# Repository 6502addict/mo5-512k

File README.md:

# mo5-512k
MO5 512K Cartridge
<br>

<br>
## Description
this cartridge is compatible with thomson MO5 64k cartridge
it's not a exact copy of the original cartridge<br>
but rather a rebuild from the manual
<br>
the $A7CB register controlling a MO5 64 cartrige is extended
to permit the access to 512k of memory
<br>
without the 3 jumpers the cartridge is behaving as the 
original thomson MEMO5 cartridge
<br>
with the jumpers set the cartridge can address 512k or memory
<br>

## Note:
The first goal of this board was to replace the original thomson board of 64K
<br>
with the use of modern chips it is easier to find a 128k or 512k chip than 64k
<br>
so I designed the 64k compatibility as the main feature and the extension
<br>
to 128k or 512k (dépending on the ram chip used AS6C1008 or AS6C4008) as goody.
<br>
Due to negative comment on forums saying that this extra memory is useless
<br>
I've listened this comments and removed the jumpers permitting to exploit
<br>
the extra memory.
<br>
As a few 512k board exist I let 512k test procedure and manual
but eagle files are now for 64k boards

## Control Register in $A7CB (without jumpers)
```
bits 0-1   bank number
bit 2      1 = ram visible
           0 = basic
bit 3      1 cartridge ram is readable and writable
           0  cartridge ram is readable and read only
bits 4-7   unused        
```

## Control Register in $A7CB (with jumpers)
```
bits 0-1   bank number
bit 2      1 = ram visible
           0 = basic
bit 3      1 cartridge ram is readable and writable
           0  cartridge ram is readable and read only
bit 4-6    extend the bank number
bit 7      unused
```

## PCB
the pcb can be ordered from oshpark<br>
https://oshpark.com/shared_projects/e0GleW5L

## Bill of Materials
* 1 x socket  dip 32  600mil
* 3 x sockets dip 20  300mil
* 1 74LS273
* 1 RAM Alliance AS6C4008
* 2 GAL Lattice 16v8D
* 1 diode 1N4148
* 5 resistor 10k    1206
* 5 capacitor 100nf 1206
* 1 block of 3 jumpers

## GAL programming
the GALS can be easily programmed with a TL866-II plus programmer<br>
GAL-16V8D-AC7B is going in the horizontal socket  (check the marking)<br>
GAL-16V8D-MO512K is going in the vertical socket

## GAL compiling
The .JED files are sufficent to build the board<br>
they can be recompiled from the .VHD by using:<br>
"Lattice ispLEVER Classic"

## Build of the board
the easiest is to solder the component in the following order<br>
1. 5 100nf capacitor (back of the board)<br>
2. 5 10k resistor (back of the board)<br>
3. 4 sockets<br
4. BC547B<br>
5. 1N4148<br>
6. jumpers<br>

## Test programs
the test program is on Daniel's web site:  http://dcmoto.free.fr/programmes/test512k-mo5/index.html

## Test procedure
follow the instructions in https://github.com/6502addict/mo5-512k/blob/main/MO5-512k/debug

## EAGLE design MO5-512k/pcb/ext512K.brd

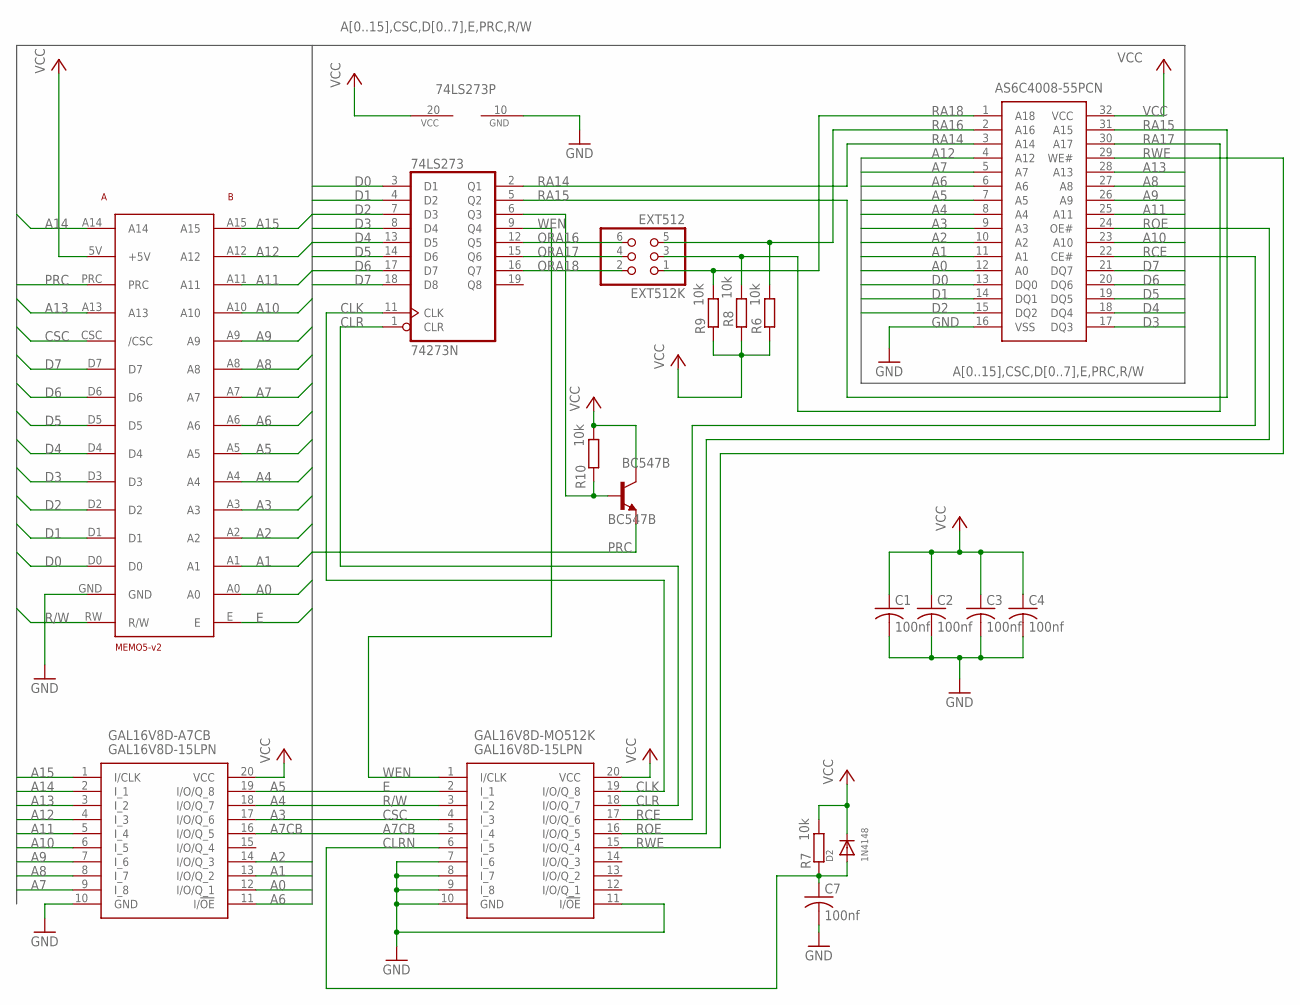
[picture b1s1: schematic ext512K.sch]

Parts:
74LS273: 74273N; DIL20
AS6C4008-55PCN: AS6C4008-55PCN; DIP1524W58P254L4191H406Q32N
BC547B: BC547B; TO92
C1, C2, C3, C4, C7: 100nf; C1206
D2: 1N4148; DO-1N4148
EXT512K: EXT512; 2X03
GAL16V8D-A7CB, GAL16V8D-MO512K: GAL16V8D-15LPN; DIP762W56P254L2591H533Q20N
R6, R7, R8, R9, R10: 10k; R1206
U$1: MEMO5-V2BRD; MEMO5-BOARD

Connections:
A0: AS6C4008-55PCN.12 (A0), GAL16V8D-A7CB.12 (I/O/Q_1), U$1.A0
A1: AS6C4008-55PCN.11 (A1), GAL16V8D-A7CB.13 (I/O/Q_2), U$1.A1
A2: AS6C4008-55PCN.10 (A2), GAL16V8D-A7CB.14 (I/O/Q_3), U$1.A2
A3: AS6C4008-55PCN.9 (A3), GAL16V8D-A7CB.17 (I/O/Q_6), U$1.A3
A4: AS6C4008-55PCN.8 (A4), GAL16V8D-A7CB.18 (I/O/Q_7), U$1.A4
A5: AS6C4008-55PCN.7 (A5), GAL16V8D-A7CB.19 (I/O/Q_8), U$1.A5
A6: AS6C4008-55PCN.6 (A6), GAL16V8D-A7CB.11 (I/!OE), U$1.A6
A7: AS6C4008-55PCN.5 (A7), GAL16V8D-A7CB.9 (I_8), U$1.A7
A7CB: GAL16V8D-A7CB.16 (I/O/Q_5), GAL16V8D-MO512K.5 (I_4)
A8: AS6C4008-55PCN.27 (A8), GAL16V8D-A7CB.8 (I_7), U$1.A8
A9: AS6C4008-55PCN.26 (A9), GAL16V8D-A7CB.7 (I_6), U$1.A9
A10: AS6C4008-55PCN.23 (A10), GAL16V8D-A7CB.6 (I_5), U$1.A10
A11: AS6C4008-55PCN.25 (A11), GAL16V8D-A7CB.5 (I_4), U$1.A11
A12: AS6C4008-55PCN.4 (A12), GAL16V8D-A7CB.4 (I_3), U$1.A12
A13: AS6C4008-55PCN.28 (A13), GAL16V8D-A7CB.3 (I_2), U$1.A13
A14: GAL16V8D-A7CB.2 (I_1), U$1.A14
A15: GAL16V8D-A7CB.1 (I/CLK), U$1.A15
CLK: 74LS273.11 (CLK), GAL16V8D-MO512K.19 (I/O/Q_8)
CLR: 74LS273.1 (CLR), GAL16V8D-MO512K.18 (I/O/Q_7)
CLRN: C7.1, D2.A, GAL16V8D-MO512K.6 (I_5), R7.1
CSC: GAL16V8D-MO512K.4 (I_3), U$1.CSC (/CSC)
D0: 74LS273.3 (D1), AS6C4008-55PCN.13 (DQ0), U$1.D0
D1: 74LS273.4 (D2), AS6C4008-55PCN.14 (DQ1), U$1.D1
D2: 74LS273.7 (D3), AS6C4008-55PCN.15 (DQ2), U$1.D2
D3: 74LS273.8 (D4), AS6C4008-55PCN.17 (DQ3), U$1.D3
D4: 74LS273.13 (D5), AS6C4008-55PCN.18 (DQ4), U$1.D4
D5: 74LS273.14 (D6), AS6C4008-55PCN.19 (DQ5), U$1.D5
D6: 74LS273.17 (D7), AS6C4008-55PCN.20 (DQ6), U$1.D6
D7: 74LS273.18 (D8), AS6C4008-55PCN.21 (DQ7), U$1.D7
E: GAL16V8D-MO512K.2 (I_1), U$1.E
GND: 74LS273.10 (GND), AS6C4008-55PCN.16 (VSS), C1.2, C2.2, C3.2, C4.2, C7.2, GAL16V8D-A7CB.10 (GND), GAL16V8D-MO512K.7 (I_6), GAL16V8D-MO512K.8 (I_7), GAL16V8D-MO512K.9 (I_8), GAL16V8D-MO512K.10 (GND), GAL16V8D-MO512K.11 (I/!OE), U$1.GND
unnamed: 74LS273.6 (Q3), BC547B.2 (B), R10.1
ORA16: 74LS273.12 (Q5), EXT512K.6
ORA17: 74LS273.15 (Q6), EXT512K.4
ORA18: 74LS273.16 (Q7), EXT512K.2
PRC: BC547B.1 (E), U$1.PRC
R/W: GAL16V8D-MO512K.3 (I_2), U$1.RW (R/W)
RA14: 74LS273.2 (Q1), AS6C4008-55PCN.3 (A14)
RA15: 74LS273.5 (Q2), AS6C4008-55PCN.31 (A15)
RA16: AS6C4008-55PCN.2 (A16), EXT512K.5, R6.2
RA17: AS6C4008-55PCN.30 (A17), EXT512K.3, R8.2
RA18: AS6C4008-55PCN.1 (A18), EXT512K.1, R9.2
RCE: AS6C4008-55PCN.22 (CE#), GAL16V8D-MO512K.17 (I/O/Q_6)
ROE: AS6C4008-55PCN.24 (OE#), GAL16V8D-MO512K.16 (I/O/Q_5)
RWE: AS6C4008-55PCN.29 (WE#), GAL16V8D-MO512K.15 (I/O/Q_4)
VCC: 74LS273.20 (VCC), AS6C4008-55PCN.32 (VCC), BC547B.3 (C), C1.1, C2.1, C3.1, C4.1, D2.C, GAL16V8D-A7CB.20 (VCC), GAL16V8D-MO512K.20 (VCC), R6.1, R7.2, R8.1, R9.1, R10.2, U$1.5V (+5V)
WEN: 74LS273.9 (Q4), GAL16V8D-MO512K.1 (I/CLK)

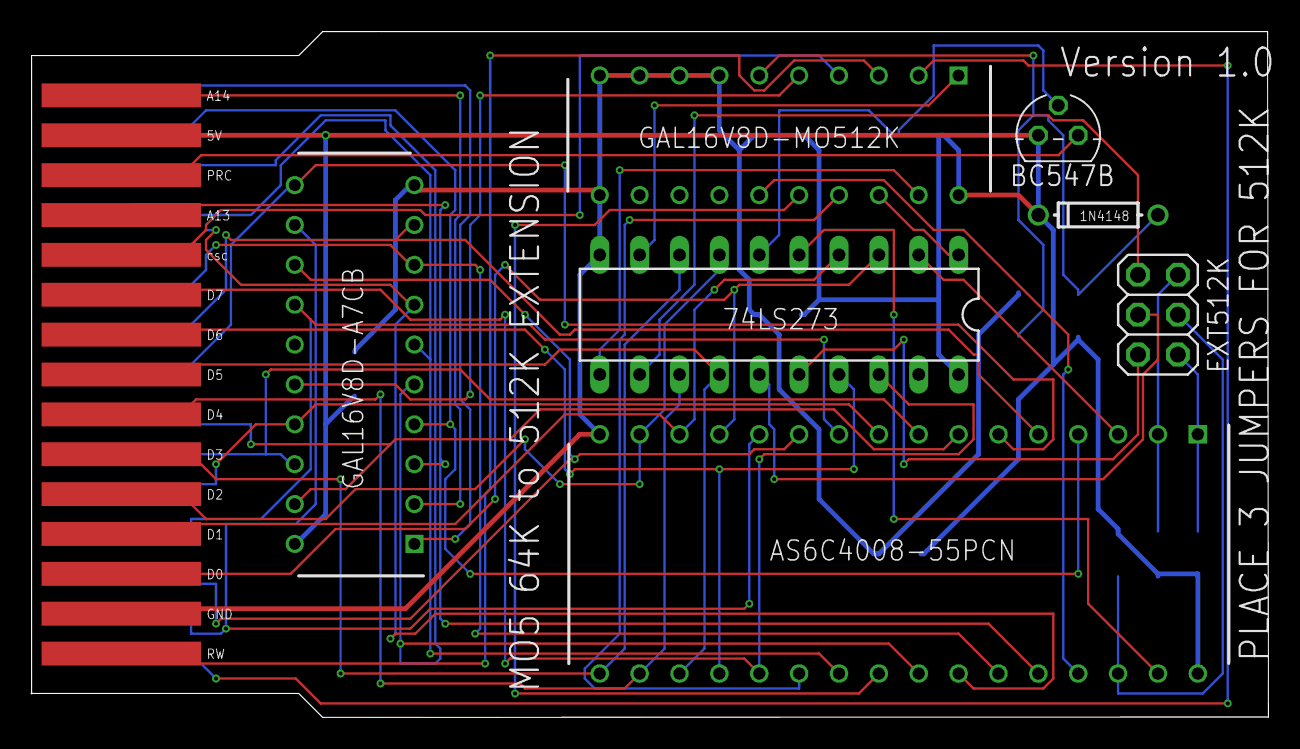
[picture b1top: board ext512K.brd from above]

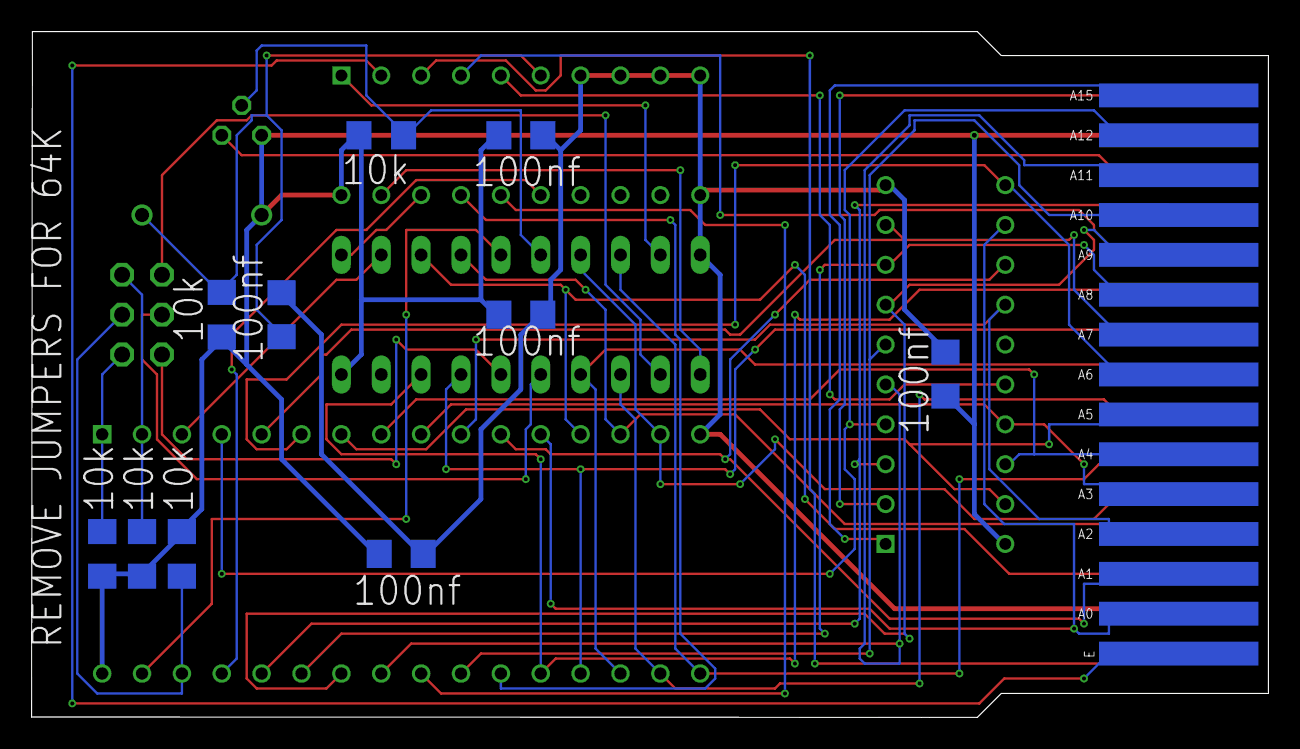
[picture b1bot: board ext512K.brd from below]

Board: 2 copper layers, 78.8 x 43.7 mm, 18 parts (10 on the bottom side), 47 nets.

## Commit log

2021-01-12 Add files via upload
    Corrected the GAL équations
2021-01-12 Add files via upload
    corrected jed files
2021-01-12 Add files via upload
    Slightly modified the bottom silk for a missing component value
    added the schematics and pcb in png format
2021-01-12 Add files via upload
    Added a photo of the board
2021-01-12 Create LICENSE
2021-01-18 Add files via upload
    commented the vhdl code to make the source more readable
2021-01-23 Update README.md
    completed the test procedure
    updated oshpark link to 64k board
2021-01-24 Add files via upload
    corrected a bug in ram control test sequence
